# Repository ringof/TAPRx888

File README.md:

CI docs for design

Source: design @ c99de62df487ad7ab04a745b40d1d9217074d0e4
Run: https://github.com/ringof/TAPRx888/actions/runs/30328942444

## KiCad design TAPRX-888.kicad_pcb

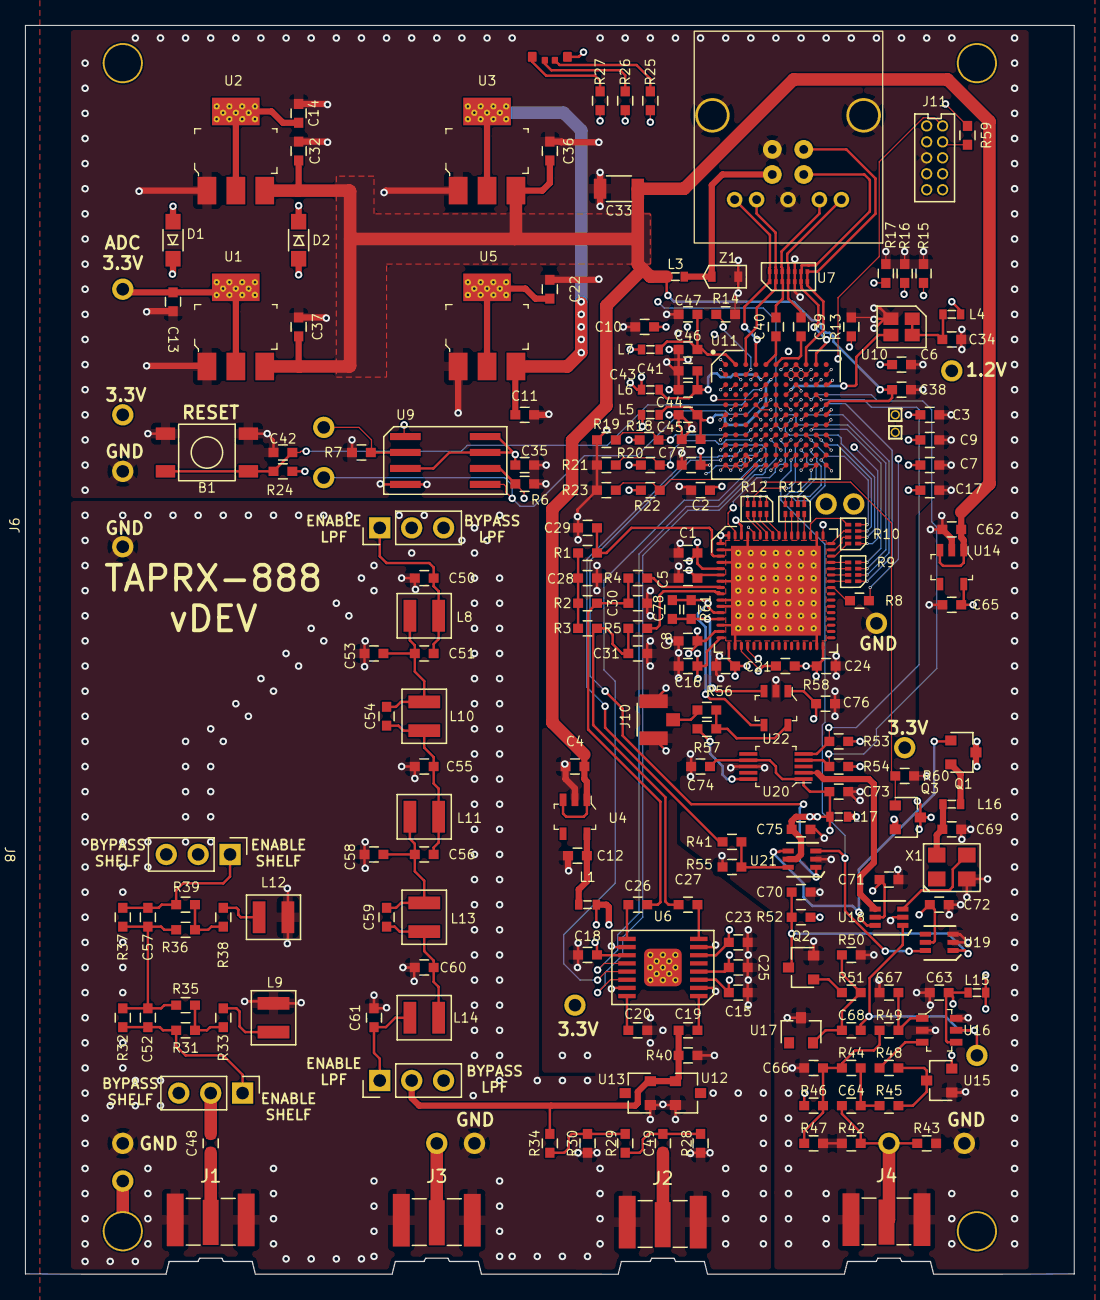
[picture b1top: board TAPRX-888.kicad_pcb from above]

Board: 6 copper layers, 83.5 x 99.4 mm, 223 parts (1 on the bottom side), 156 nets.

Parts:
B1: BUTTON-4p5X4p5
C1, C2, C3, C5, C6, C7, C8, C9, C10, C15, C16, C17, C18, C19, C20, C21, C23, C24, C26, C27, C28, C32, C34, C35, C36, C37, C38, C39, C40, C42, C43, C44, C46, C48, C49, C63, C64, C66, C67, C68, C69, C70, C71, C72, C73, C74, C75, C76, C77: C-0.1-0603; C_0603
C4, C25, C62: C-1u-0603; C_0603
C11, C12, C13, C14, C29, C65: C-10u-0603; C_0603
C22, C41, C45, C47: C-22u-0603; C_0603
C30, C31: C-4.7p-0603; C_0603
C33: C-10u-50V-1206; PAD_1206
C50, C61: C-56p-0603; C_0603
C51: C-12p-0603; C_0603
C52, C57: C-330p-0603; C_0603
C53: C-82p-0603; C_0603
C54: C-39p-0603; C_0603
C55, C58: C-68p-0603; C_0603
C56: C-47p-0603; C_0603
C59: C-22p-0603; C_0603
C60: C-100p-0603; C_0603
C78: C-8.2p-0603; C_0603
D1, D2: Schottky_Pwr_B5819W; SOD-123
D3: LED_RGB_SIDE
H1, H2, H3, H4: MountingHole_M2.5-PTH
J1, J2, J3, J4: CONN_SMA_JACK_EDGE_JLC_With_Nut; SMA_Jack_EdgeMount_JLC_With_Nut
J5: USB-3.0
J6, J7, J8, J9: Conn_01x03; Pin_Header_Straight_1x03_Pitch2.54mm
J10: U.FL-R; HRS_U.FL-R-SMT(01)
J11: Conn_JTAG10-mini; CONN-JTAG10-mini
L1, L4, L5, L6, L7, L15, L16, L17: FBEAD0603-1u-190mA; 0603
L2: TIS_LOGO; TIS-Logo
L3: FBEAD0603_2A; 0603
L8: Inductor-180n-1008; Murata2U
L9, L12: Inductor-820n-1008; Murata2U
L10, L11: Inductor-120n-1008; Murata2U
L13, L14: Inductor-150n-1008; Murata2U
Q1, Q3: PMOS Si2343DS; SOT-23
Q2: MMBT3904; SOT-23
R1, R4, R5: R-4.7-0603; PAD_0603
R2, R3: R-47Ω-0603; PAD_0603
R6, R24: R-100K-0603; PAD_0603
R7: R-2.0K-0603; PAD_0603
R8, R56, R57: R-22Ω-0603; PAD_0603
R9, R10, R11, R12: R-22 0402x4; 4D02
R13: R-6.04K-0603; PAD_0603
R14: R-200-0603; PAD_0603
R15, R16, R17, R25, R26, R27: R-1K-0603; PAD_0603
R18, R19, R20, R21, R22, R23: R-0Ω-0603; PAD_0603
R28, R30, R31, R35, R36, R39: R-51Ω-0603; PAD_0603
R29, R34, R53, R54: R-2.2K-0603; PAD_0603
R32, R37: R-220Ω-0603; PAD_0603
R33, R38: R-10Ω-0603; PAD_0603
R40, R41, R42, R43, R61: R-100-0603; PAD_0603
R44, R49, R50: R-1M-0603; PAD_0603
R45, R48: R-330Ω-0603; PAD_0603
R46, R47, R51, R52, R55, R60: R-10K-0603; PAD_0603
R58, R59: R-47K-0603; PAD_0603
TP1, TP2, TP3, TP4, TP5, TP6, TP7, TP8, TP9, TP10, TP11, TP12, TP13, TP14, TP15, TP16, TP17, TP18, TP19: TP
TP20, TP21: TP-TINY; TP-Tiny
U1, U2, U3: AP2114H-3.3TRG1; SOT-223_THERMAL
U4, U14: LP5907MFX-3.3; SOT-23-5
U5: UMW AMS1117-1.2; SOT-223_THERMAL
U6: AD8370; TSSOP-16-Thermal
U7: TVS-SP3011; SP3011
U8: LTC2208CUP#PBF; QFN-64_EP_9.5x9.5_Pitch0.5mm
U9: MX25L3233FM2I; SOIC-8-dual
U10: XO-19.2MHZ; SMD-2520
U11: CYUSB3014-BZXCT; BGA-121
U12, U13, U15, U17: SOT-23
U16: TLV3501; SOT-23-6
U18, U21: NC7SV157; SC-70-6
U19: 74LVC2G14; SC-70-6_rot90
U20: Si5351A; MSOP-10_W3mm
U22: SN65LVDS1; SOT-23-5
X1: TCXO-27M; TCXO-3225
Z1: PESD5V0U1UA; SOD-323

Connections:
3V3REF: C65.1, L15.2, Q1.3 (D), Q3.3 (D), R53.2, R54.2, TP17.1, U14.5 (OUT)
+1V2: C3.2, C7.2, C10.2, C22.1, C77.2, L6.1, L7.1, TP6.1, U5.2 (OUT), U5.4 (OUT), U11.A7 (AVDD), U11.B10 (VDD@1), U11.C3 (VDD@2), U11.E9 (VDD@3), U11.F11 (VDD@4), U11.H1 (VDD@5), U11.J11 (VDD@7), U11.L5 (VDD@8), U11.L7 (VDD@6)
+3V3: C2.2, C6.2, C9.2, C14.1, C17.2, C35.2, C72.1, D1.2 (A), D2.1 (K), D3.1 (C), J11.1, L4.2, L5.1, R18.2, R20.2, R22.2, R24.1, R52.1, R59.1, TP5.1, U2.2 (OUT), U2.4 (OUT), U9.3 (WPN), U9.7 (HOLDN), U9.8 (VDD), U11.B1 (VIO4), U11.C11 (VIO5), U11.E3 (VIO3), U11.E6 (FSLC[2]), U11.E10 (VBAT), U11.F1 (VIO2), U11.H11 (VIO1@1), U11.L9 (VIO1@2), U19.5 (VCC)
+3V3ADC: C1.2, C5.2, C8.2, C13.1, C16.2, C21.2, C24.2, D1.1 (K), D2.2 (A), R58.1, TP4.1, U1.2 (OUT), U1.4 (OUT), U8.1 (SENSE), U8.5 (VDD_5), U8.6 (VDD), U8.15 (VDD_2), U8.16 (VDD_3), U8.17 (VDD_4), U8.32 (OVDD), U8.49 (OVDD_2), U8.62 (MODE), U8.64 (PGA)
/3.3V-PRE: C11.1, U3.2 (OUT), U3.4 (OUT), U5.3 (IN)
/CLKIN: U10.3 (OUT), U11.D7 (CLKIN)
/Clock/AUTOCLK_N: R41.1, U11.J3 (GPIO37)
/Clock/CLK0: R57.2, U20.10 (CLK0)
/Clock/CLKGEN3.3V: C71.1, C73.2, C74.2, C75.1, C76.1, L17.1, U18.5 (VCC), U20.1 (VDD), U20.7 (VDDO), U21.5 (VCC), U22.1 (VCC)
/Clock/EXTCLKSEL_N: U11.K1 (GPIO35), U21.1 (IN1)
/Clock/EXT_REF_IN: C64.2, J4.1 (In), R42.1, R43.1, TP15.1
/Clock/REFCLK3.3V: C63.2, L15.1, R46.1, U15.2, U16.4 (V+)
/Clock/Vdd5351: L17.2, Q3.2 (S)
/D0: R9.1, U11.F10 (GPIO0)
/D1: R9.2, U11.F9 (GPIO1)
/D2: R9.3, U11.F7 (GPIO2)
/D3: R9.4, U11.G10 (GPIO3)
/D4: R10.1, U11.G9 (GPIO4)
/D5: R10.2, U11.F8 (GPIO5)
/D6: R10.3, U11.H10 (GPIO6)
/D7: R10.4, U11.H9 (GPIO7)
/D8: R11.1, U11.J10 (GPIO8)
/D9: R11.2, U11.J9 (GPIO9)
/D10: R11.3, U11.K11 (GPIO10)
/D11: R11.4, U11.L10 (GPIO11)
/D12: R12.1, U11.K10 (GPIO12)
/D13: R12.2, U11.K9 (GPIO13)
/D14: R12.3, U11.J8 (GPIO14)
/D15: R12.4, U11.G8 (GPIO15)
/DIS_5351: Q3.1 (G), R60.1, U11.J4 (GPIO34)
/DITH: U8.20 (DITH), U11.H5 (GPIO29)
/EXT_REF_ACTIVE: U11.K8 (GPIO17), U19.6, U21.3 (IN0)
/Front_End_Filter/FILTER_OUT: C19.1, J9.2, R34.2, R40.1, U12.1, U13.2
/Front_End_Filter/RF_ATTEN__IN: C49.1, J2.1 (In)
/Front_End_Filter/RF_IN: C48.1, J1.1 (In)
/ID0: R15.1, U11.K2 (GPIO33)
/ID1: R16.1, U11.J2 (GPIO36)
/ID2: R17.1, U11.F2 (GPIO45)
/ID5: R26.1, U11.F4 (GPIO41)
/ID6: R25.1, U11.G6 (GPIO22)
/ID7: R27.1, U11.G7 (GPIO21)
/OVFL: U8.60 (OF+/OFA), U11.G5 (GPIO25)
/PCLK: R8.2, U11.J6 (GPIO16)
/PMODE0: R18.1, R19.1, U11.G4 (GPIO30)
/PMODE1: R20.1, R21.1, U11.H4 (GPIO31)
/PMODE2: R22.1, R23.1, U11.L4 (GPIO32)
/RAND: U8.63 (RAND), U11.H7 (GPIO20)
/RESET_N: B1.3, B1.4, C42.2, J11.10, R24.2, U11.C5 (RESET)
/SAMPLE_CLK_N: C78.2, R61.2, U8.13 (ENC-), U22.3
/SAMPLE_CLK_P: C78.1, R61.1, U8.12 (ENC+), U22.4
/SCL: R54.1, U11.D9 (I2C_GPIO[58]), U20.4 (SCL)
/SDA: R53.1, U11.D10 (I2C_GPIO[59]), U20.5 (SDA)
/SHDN: R58.2, U8.19 (SHDN), U11.J5 (GPIO28)
/SPI_MISO: R7.1, TP9.1, U9.2 (SO), U11.C2 (GPIO55)
/SPI_MOSI: TP10.1, U9.5 (SI), U11.D5 (GPIO56)
/SPI_SCK: R6.1, U9.6 (SCLK), U11.D4 (GPIO53)
/SPI_SSN: U9.1 (CSN), U11.C1 (GPIO54)
/SSRX+: J5.9 (SSRX+), U7.1, U7.14, U11.A4 (SSRXP)
/SSRX-: J5.8 (SSRX-), U7.2, U7.13, U11.A3 (SSRXM)
/SSTX+: C40.1, J5.6 (SSTX+), U7.3, U7.12
/SSTX-: C39.1, J5.5 (SSTX-), U7.4, U7.11
/TCK: J11.4, U11.F6 (TCK)
/TDI: J11.8, U11.E7 (TDI)
/TDO: J11.6, U11.C10 (TDO)
/TMS: J11.2, U11.E8 (TMS)
/TRST: J11.9, R59.2, U11.B11 (TRST)
/USB+: J5.3 (D+), U7.7, U7.8, U11.A9 (DP)
/USB-: J5.2 (D-), U7.6, U7.9, U11.A10 (DM)
/VBUS: C4.1, C32.2, C33.1, C36.2, C37.2, C38.2, C62.1, L3.2, U1.3 (IN), U2.3 (IN), U3.3 (IN), U4.1 (IN), U4.3 (ENA), U11.E11 (VBUS), U14.1 (IN), U14.3 (ENA)
/VCM: C29.1, R1.1, U8.3 (VCM)
/VGA3.3V: C15.2, C18.2, C23.2, C25.1, L1.2, TP3.1, U6.3 (VCCI), U6.4 (PWUP), U6.6 (VCCO), U6.11 (VCCO)
/VGA_CLK: U6.13 (CLK), U11.K5 (GPIO27)
/VGA_D: U6.14 (D), U11.H6 (GPIO26)
/VGA_LE: U6.12 (LE), U11.J1 (GPIO38)
GND: B1.1, B1.2, C1.1, C2.1, C3.1, C4.2, C5.1, C6.1, C7.1, C8.1, C9.1, C10.1, C11.2, C12.2, C13.2, C14.2, C15.1, C16.1, C17.1, C18.1, C20.2, C21.1, C22.2, C23.1, C24.1, C25.2, C28.1, C29.2, C30.2, C31.2, C32.1, C33.2, C34.1, C35.1, C36.1, C37.1, C38.1, C41.2, C42.1, C43.1, C44.1, C45.2, C46.1, C47.2, C50.2, C53.2, C55.2, C58.2, C60.2, C61.2, C62.2, C63.1, C65.2, C66.2, C67.2, C69.1, C70.2, C71.2, C72.2, C73.1, C74.1, C75.2, C76.2, C77.1, J1.2 (Ext), J2.2 (Ext), J3.2 (Ext), J4.2 (Ext), J5.0 (SHELL), J5.4 (GND), J5.7 (SIG_GND), J10.2 (Ext), J11.3, L9.1, L12.1, Q2.2 (E), R6.2, R7.2, R13.2, R14.2, R15.2, R16.2, R17.2, R19.2, R21.2, R23.2, R28.2, R30.2, R40.2, R42.2, R43.2, R47.2, R50.2, R55.2, R60.2, TP2.1, TP7.1, TP8.1, TP14.1, TP16.1, TP19.1, U1.1 (GND), U2.1 (GND), U3.1 (GND), U4.2 (GND), U5.1 (GND), U6.2 (ICOM), U6.7 (OCOM), U6.10 (OCOM), U6.15 (ICOM), U7.5, U7.10, U8.2 (GND_6), U8.4 (GND_2), U8.7 (GND_4), U8.10 (GND_5), U8.11 (GND_7), U8.14 (GND_3), U8.18 (GND), U8.31 (OGND_2), U8.50 (OGND), U8.61 (LVDS), U8.65 (EP), U9.4 (VSS), U10.2 (GND), U11.A1 (U3VSSQ), U11.A8 (VSS@14), U11.B2 (FSLC[0]), U11.B4 (FSLC[1]), U11.B7 (AVSS), U11.B8 (VSS@8), U11.B9 (VSS@9), U11.D8 (VSS@1), U11.E2 (VSS@2), U11.G1 (VSS@3), U11.G11 (VSS@4), U11.K3 (VSS@12), U11.K4 (VSS@10), U11.L1 (VSS@5), U11.L2 (VSS@13), U11.L3 (VSS@11), U11.L6 (VSS@6), U11.L11 (VSS@7), U12.2, U13.1, U14.2 (GND), U15.1, U16.2 (V-), U16.6 (SHDN), U17.3, U18.2 (GND), U19.2 (GND), U19.3, U20.8 (GND), U21.2 (GND), U22.2 (GND), X1.2 (GND), Z1.2
unnamed: C26.2, C30.1, R2.1, R4.1
unnamed: C27.2, C31.1, R3.2, R5.1
unnamed: C28.2, R1.2, R2.2, R3.1
unnamed: C49.2, R28.1, R29.1
unnamed: C51.2, C53.1, C54.1, L8.2, L10.1
unnamed: C52.2, C57.1, R32.2, R35.2, R36.1, R37.1
unnamed: C54.2, C55.1, C56.1, L10.2, L11.1
unnamed: C56.2, C58.1, C59.1, L11.2, L13.1
unnamed: C59.2, C60.1, L13.2, L14.1
unnamed: C64.1, R44.2, R45.2
unnamed: C66.1, R44.1, R46.2, R47.1, R49.1
unnamed: C68.1, R50.1, R51.2, U17.2
unnamed: D3.2 (B), R25.2
unnamed: D3.3 (G), R26.2
unnamed: D3.4 (R), R27.2
unnamed: H1.1, TP13.1
unnamed: J3.1 (In), TP1.1
unnamed: J5.1 (V+), L3.1, Z1.1
unnamed: C50.1, C51.1, J6.1, L8.1
unnamed: J6.2, J8.2
unnamed: J6.3, J9.3
unnamed: C52.1, J7.1, R31.1, R32.1
unnamed: C48.2, J7.2
unnamed: J7.3, J8.3
unnamed: C57.2, J8.1, R37.2, R39.2
unnamed: C61.1, J9.1, L14.2
unnamed: J10.1 (In), R56.1
unnamed: L9.2, R33.2
unnamed: L12.2, R38.2
unnamed: Q1.1 (G), U18.6 (SEL), U21.4 (Z)
unnamed: L16.2, Q1.2 (S)
unnamed: Q2.1 (B), R51.1
unnamed: C70.1, Q2.3 (C), R52.2, U19.1
unnamed: R29.2, R30.1, R34.1
unnamed: R31.2, R33.1, R35.1
unnamed: R36.2, R38.1, R39.1
unnamed: R45.1, R48.2, U15.3
unnamed: R56.2, R57.1, U22.5
unnamed: C12.1, L1.1, U4.5 (OUT)
unnamed: C19.2, U6.1 (IN+)
unnamed: C20.1, U6.16 (IN-)
unnamed: C27.1, U6.8 (OUT+)
unnamed: C26.1, U6.9 (OUT-)
unnamed: R4.2, U8.8 (AIN+)
unnamed: R5.2, U8.9 (AIN-)
unnamed: R9.8, U8.42 (D8+/DA0)
unnamed: R8.1, U8.41 (D8-/CLKOUTA)
unnamed: R9.6, U8.44 (D9+/DA2)
unnamed: R9.7, U8.43 (D9-/DA1)
unnamed: R10.8, U8.46 (D10+/DA4)
unnamed: R9.5, U8.45 (D10-/DA3)
unnamed: R10.6, U8.48 (D11+/DA6)
unnamed: R10.7, U8.47 (D11-/DA5)
unnamed: R11.8, U8.52 (D12+/DA8)
unnamed: R10.5, U8.51 (D12-_/DA7)
unnamed: R11.6, U8.54 (D13+/DA10)
unnamed: R11.7, U8.53 (D13-/DA9)
unnamed: R12.8, U8.56 (D14+/DA12)
unnamed: R11.5, U8.55 (D14-/DA11)
unnamed: R12.6, U8.58 (D15+/DA14)
unnamed: R12.7, U8.57 (D15-/DA13)
unnamed: R12.5, U8.59 (OF-/DA15)
unnamed: C34.2, L4.1, U10.1 (TS-N), U10.4 (VDD)
unnamed: C44.2, C45.1, L5.2, U11.B6 (CVDDQ)
unnamed: TP11.1, U11.K7 (GPIO18)
unnamed: TP12.1, U11.J7 (GPIO19)
unnamed: TP20.1, U11.E5 (GPIO48)
unnamed: TP21.1, U11.E4 (GPIO49)
unnamed: R13.1, U11.C8 (R_USB2)
unnamed: R14.1, U11.B3 (R_USB3)
unnamed: C39.2, U11.A6 (SSTXM)
unnamed: C40.2, U11.A5 (SSTXP)
unnamed: C46.2, C47.1, L7.2, U11.A2 (U3RXVDDQ)
unnamed: C41.1, C43.2, L6.2, U11.B5 (U3TXVDDQ)
unnamed: R48.1, U16.3 (IN+)
unnamed: C67.1, R49.2, U16.1 (IN-)
unnamed: C68.2, TP18.1, U16.5 (OUT), U18.1 (IN1)
unnamed: U18.3 (IN0), X1.3 (OUT)
unnamed: U18.4 (Z), U20.2 (XA)
unnamed: R41.2, R55.1, U21.6 (SEL)
unnamed: C69.2, L16.1, X1.4 (VDD)

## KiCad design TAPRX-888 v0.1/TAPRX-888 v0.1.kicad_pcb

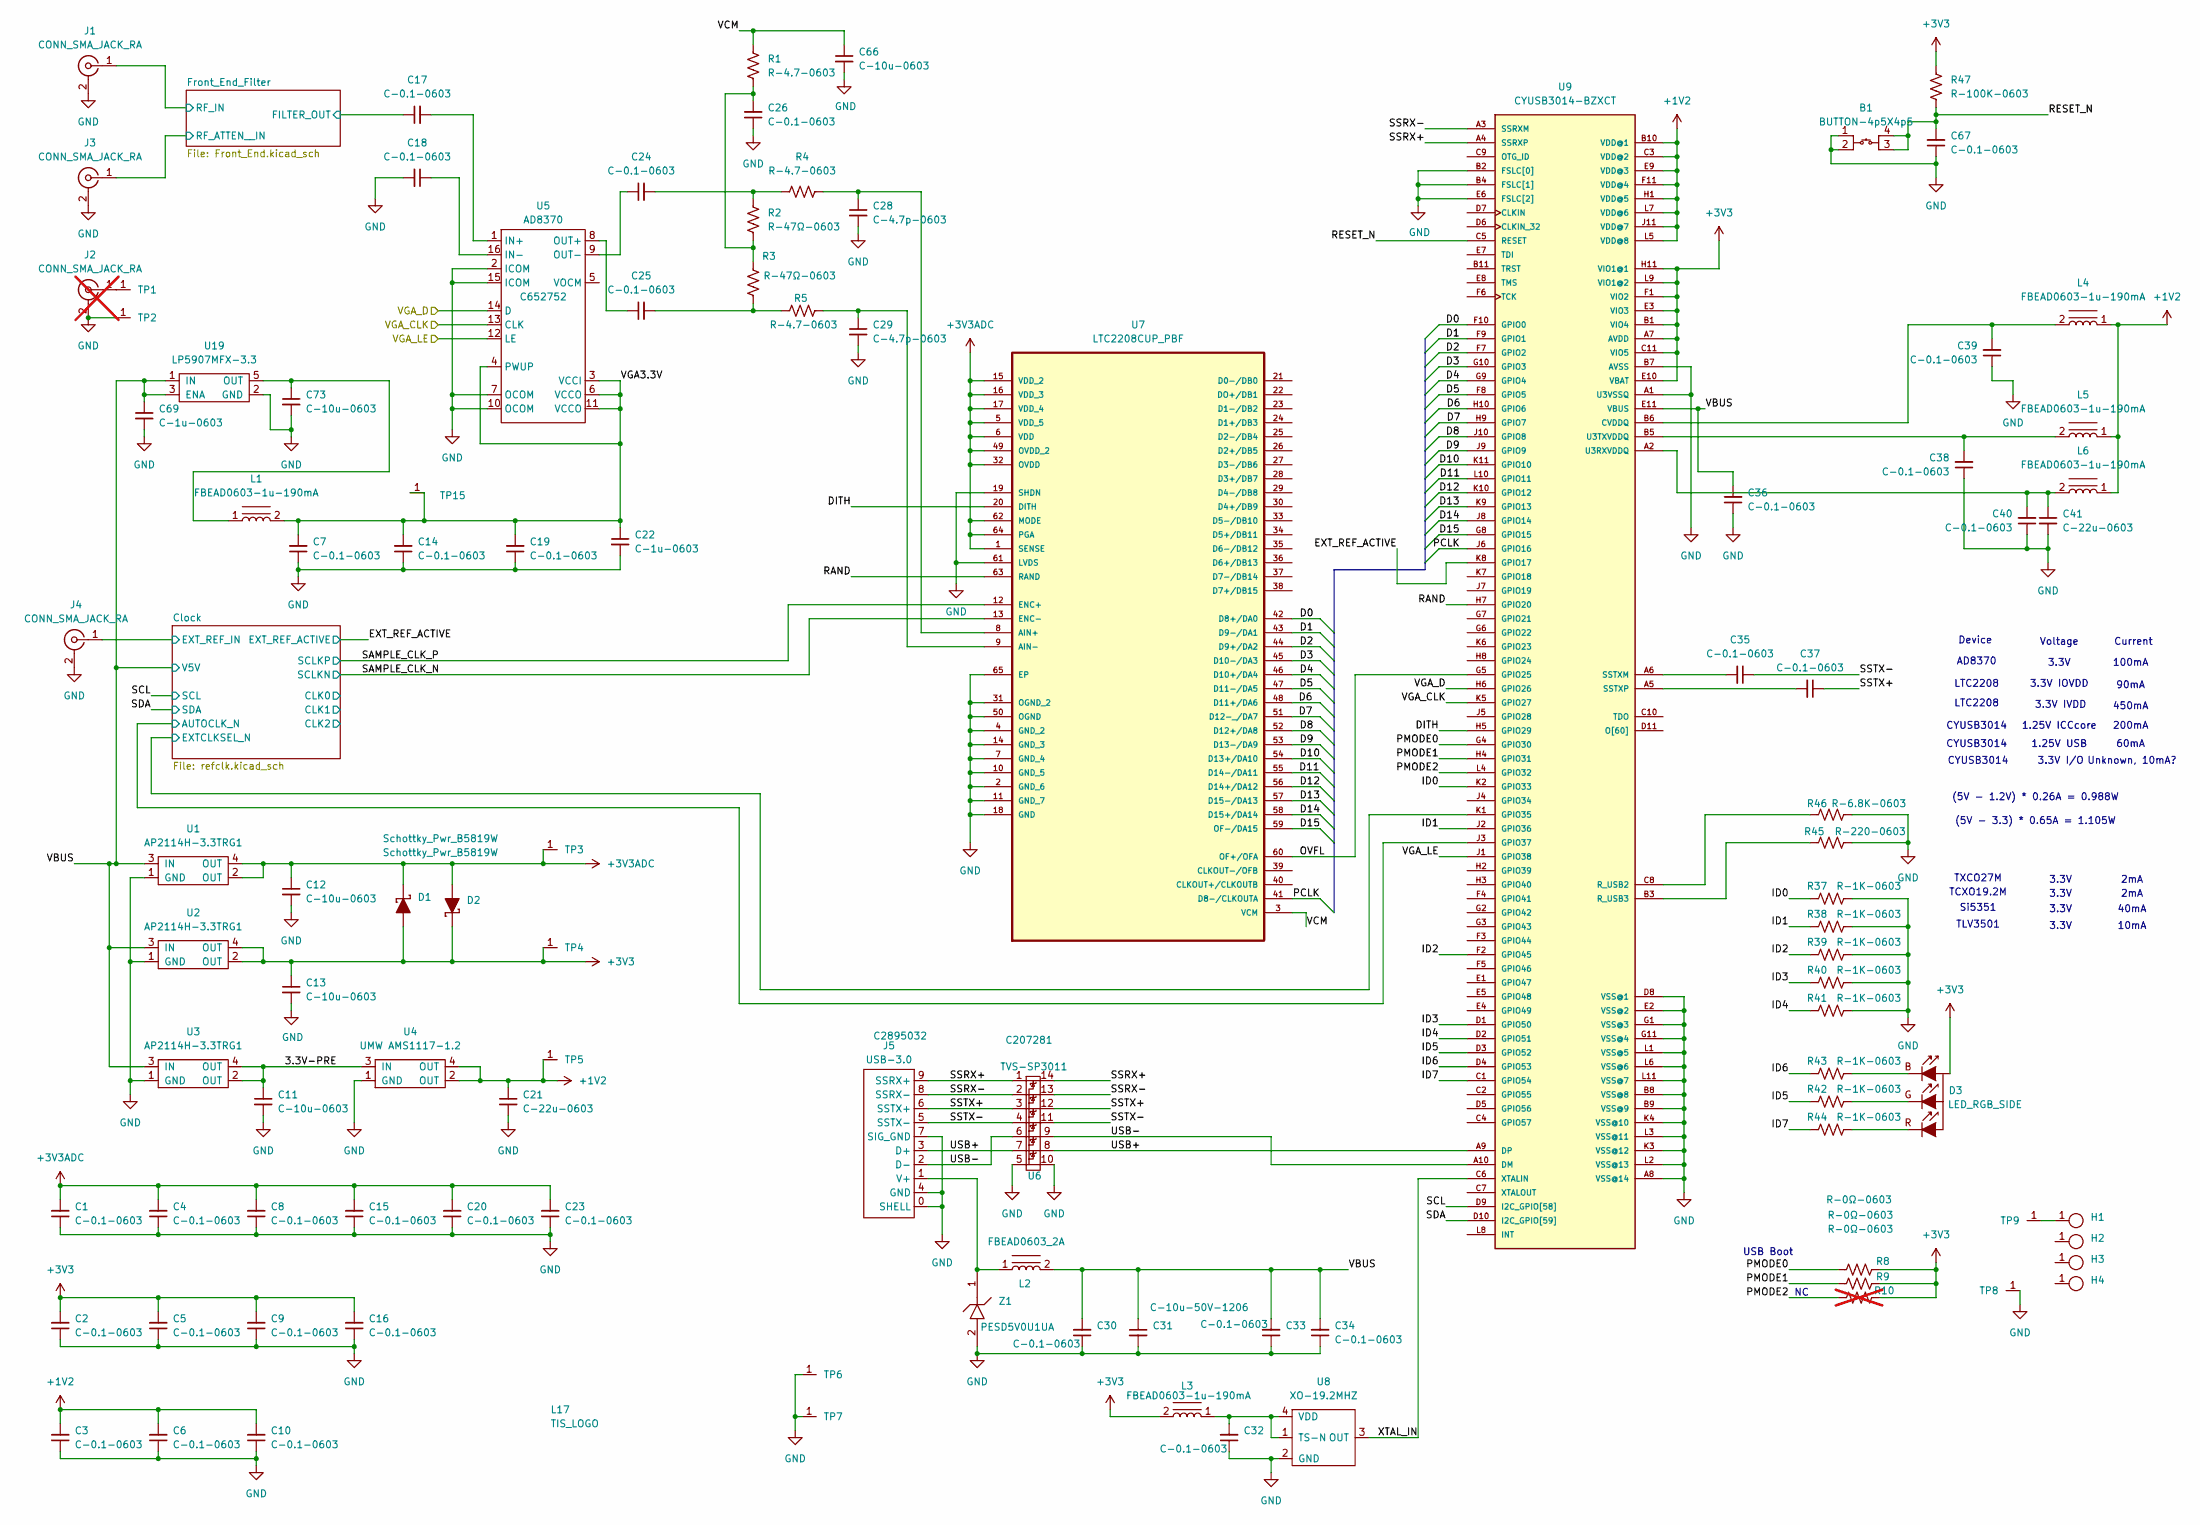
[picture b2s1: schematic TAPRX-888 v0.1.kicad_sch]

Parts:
B1: BUTTON-4p5X4p5; LCSC Part # C410371
C1, C2, C3, C4, C5, C6, C7, C8, C9, C10, C14, C15, C16, C17, C18, C19, C20, C23, C24, C25, C26, C30, C32, C33, C34, C35, C36, C37, C38, C39, C40, C67: C-0.1-0603; C_0603; LCSC Part # C14663
C11, C12, C13, C66, C73: C-10u-0603; PAD_0603; LCSC Part # C96446
C21, C41: C-22u-0603; PAD_0603; LCSC Part # C59461
C22, C69: C-1u-0603; PAD_0603; LCSC Part # C15849
C28, C29: C-4.7p-0603; C_0603; LCSC Part # C1669
C31: C-10u-50V-1206; PAD_1206; LCSC Part # C13585
D1, D2: Schottky_Pwr_B5819W; SOD-123; LCSC Part # C8598
D3: LED_RGB_SIDE; LCSC Part # C389528
H1, H2, H3, H4: MountingHole_M2.5-PTH
J1, J3, J4: CONN_SMA_JACK_RA; SMA-RA-Jack; LCSC Part # C91455
J2: CONN_SMA_JACK_RA; SMA-RA-Jack; LCSC Part # C91455; not fitted
J5: USB-3.0; LCSC Part # C2895032
L1, L3, L4, L5, L6: FBEAD0603-1u-190mA; 0603; LCSC Part # C307748
L2: FBEAD0603_2A; 0603; LCSC Part # C14709
L17: TIS_LOGO; TIS-Logo
R1, R4, R5: R-4.7-0603; PAD_0603; LCSC Part # C23164
R2, R3: R-47Ω-0603; PAD_0603; LCSC Part # C23179
R8, R9: R-0Ω-0603; PAD_0603; LCSC Part # C21189
R10: R-0Ω-0603; PAD_0603; LCSC Part # C21189; not fitted
R37, R38, R39, R40, R41, R42, R43, R44: R-1K-0603; PAD_0603; LCSC Part # C21190
R45: R-220-0603; PAD_0603; LCSC Part # C107696
R46: R-6.8K-0603; PAD_0603; LCSC Part # C114632
R47: R-100K-0603; PAD_0603; LCSC Part # C25803
TP1, TP2, TP3, TP4, TP5, TP6, TP7, TP8, TP9, TP15: TP
U1, U2, U3: AP2114H-3.3TRG1; SOT-223_THERMAL; LCSC Part # C150716
U4: UMW AMS1117-1.2; SOT-223_THERMAL; LCSC Part # C347218
U5: AD8370; TSSOP-16-Thermal; LCSC Part # C652752
U6: TVS-SP3011; SP3011; LCSC Part # C207281
U7: LTC2208CUP_PBF; QFN-64_EP_9.5x9.5_Pitch0.5mm; MPN LTC2208CUP#PBF#PBF; LCSC Part # C679544
U8: XO-19.2MHZ; SMD-2520; LCSC Part # C49304731
U9: CYUSB3014-BZXCT; BGA-121; DigiKey_Part_Number 448-CYUSB3014-BZXCTTR-ND
U19: LP5907MFX-3.3; SOT-23-5; LCSC Part # C80670
Z1: PESD5V0U1UA; SOD-323; LCSC Part # C5380401

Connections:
+1V2: C3.2, C6.2, C10.2, C21.1, L4.1, L5.1, L6.1, TP5.1, U4.2 (OUT), U4.4 (OUT), U9.B10 (VDD@1), U9.C3 (VDD@2), U9.E9 (VDD@3), U9.F11 (VDD@4), U9.H1 (VDD@5), U9.J11 (VDD@7), U9.L5 (VDD@8), U9.L7 (VDD@6)
+3V3: C2.2, C5.2, C9.2, C13.1, C16.2, D1.2 (A), D2.1 (K), D3.1 (C), L3.2, R8.2, R9.2, R10.2, R47.1, TP4.1, U2.2 (OUT), U2.4 (OUT), U9.A7 (AVDD), U9.B1 (VIO4), U9.C11 (VIO5), U9.E3 (VIO3), U9.E10 (VBAT), U9.F1 (VIO2), U9.H11 (VIO1@1), U9.L9 (VIO1@2); also elsewhere on the board
+3V3ADC: C1.2, C4.2, C8.2, C12.1, C15.2, C20.2, C23.2, D1.1 (K), D2.2 (A), TP3.1, U1.2 (OUT), U1.4 (OUT), U7.1 (SENSE), U7.5 (VDD_5), U7.6 (VDD), U7.15 (VDD_2), U7.16 (VDD_3), U7.17 (VDD_4), U7.32 (OVDD), U7.49 (OVDD_2), U7.62 (MODE), U7.64 (PGA)
/3.3V-PRE: C11.1, U3.2 (OUT), U3.4 (OUT), U4.3 (IN)
/Clock/AUTOCLK_N: U9.J3 (GPIO37); also elsewhere on the board
/Clock/EXTCLKSEL_N: U9.K1 (GPIO35); also elsewhere on the board
/Clock/EXT_REF_IN: J4.1 (In); also elsewhere on the board
/D0: U7.42 (D8+/DA0), U9.F10 (GPIO0)
/D1: U7.43 (D9-/DA1), U9.F9 (GPIO1)
/D2: U7.44 (D9+/DA2), U9.F7 (GPIO2)
/D3: U7.45 (D10-/DA3), U9.G10 (GPIO3)
/D4: U7.46 (D10+/DA4), U9.G9 (GPIO4)
/D5: U7.47 (D11-/DA5), U9.F8 (GPIO5)
/D6: U7.48 (D11+/DA6), U9.H10 (GPIO6)
/D7: U7.51 (D12-_/DA7), U9.H9 (GPIO7)
/D8: U7.52 (D12+/DA8), U9.J10 (GPIO8)
/D9: U7.53 (D13-/DA9), U9.J9 (GPIO9)
/D10: U7.54 (D13+/DA10), U9.K11 (GPIO10)
/D11: U7.55 (D14-/DA11), U9.L10 (GPIO11)
/D12: U7.56 (D14+/DA12), U9.K10 (GPIO12)
/D13: U7.57 (D15-/DA13), U9.K9 (GPIO13)
/D14: U7.58 (D15+/DA14), U9.J8 (GPIO14)
/D15: U7.59 (OF-/DA15), U9.G8 (GPIO15)
/DITH: U7.20 (DITH), U9.H5 (GPIO29)
/EXT_REF_ACTIVE: U9.K8 (GPIO17); also elsewhere on the board
/Front_End_Filter/FILTER_OUT: C17.1; also elsewhere on the board
/Front_End_Filter/RF_ATTEN__IN: J3.1 (In); also elsewhere on the board
/Front_End_Filter/RF_IN: J1.1 (In); also elsewhere on the board
/ID0: R37.1, U9.K2 (GPIO33)
/ID1: R38.1, U9.J2 (GPIO36)
/ID2: R39.1, U9.F2 (GPIO45)
/ID3: R40.1, U9.D1 (GPIO50)
/ID4: R41.1, U9.D2 (GPIO51)
/ID5: R42.1, U9.D3 (GPIO52)
/ID6: R43.1, U9.D4 (GPIO53)
/ID7: R44.1, U9.C1 (GPIO54)
/OVFL: U7.60 (OF+/OFA), U9.G5 (GPIO25)
/PCLK: U7.41 (D8-/CLKOUTA), U9.J6 (GPIO16)
/PMODE0: R8.1, U9.G4 (GPIO30)
/PMODE1: R9.1, U9.H4 (GPIO31)
/PMODE2: R10.1, U9.L4 (GPIO32)
/RAND: U7.63 (RAND), U9.H7 (GPIO20)
/RESET_N: B1.3, B1.4, C67.2, R47.2, U9.C5 (RESET)
/SAMPLE_CLK_N: U7.13 (ENC-); also elsewhere on the board
/SAMPLE_CLK_P: U7.12 (ENC+); also elsewhere on the board
/SCL: U9.D9 (I2C_GPIO[58]); also elsewhere on the board
/SDA: U9.D10 (I2C_GPIO[59]); also elsewhere on the board
/SSRX+: J5.9 (SSRX+), U6.1, U6.14, U9.A4 (SSRXP)
/SSRX-: J5.8 (SSRX-), U6.2, U6.13, U9.A3 (SSRXM)
/SSTX+: C37.1, J5.6 (SSTX+), U6.3, U6.12
/SSTX-: C35.1, J5.5 (SSTX-), U6.4, U6.11
/USB+: J5.3 (D+), U6.7, U6.8, U9.A9 (DP)
/USB-: J5.2 (D-), U6.6, U6.9, U9.A10 (DM)
/VBUS: C30.2, C31.1, C33.2, C34.2, C36.2, C69.1, L2.2, U1.3 (IN), U2.3 (IN), U3.3 (IN), U9.E11 (VBUS), U19.1 (IN), U19.3 (ENA); also elsewhere on the board
/VCM: C66.1, R1.1, U7.3 (VCM)
/VGA3.3V: C7.2, C14.2, C19.2, C22.1, L1.2, TP15.1, U5.3 (VCCI), U5.4 (PWUP), U5.6 (VCCO), U5.11 (VCCO)
/VGA_CLK: U5.13 (CLK), U9.K5 (GPIO27)
/VGA_D: U5.14 (D), U9.H6 (GPIO26)
/VGA_LE: U5.12 (LE), U9.J1 (GPIO38)
/XTAL_IN: U8.3 (OUT), U9.C6 (XTALIN)
GND: B1.1, B1.2, C1.1, C2.1, C3.1, C4.1, C5.1, C6.1, C7.1, C8.1, C9.1, C10.1, C11.2, C12.2, C13.2, C14.1, C15.1, C16.1, C18.2, C19.1, C20.1, C21.2, C22.2, C23.1, C26.1, C28.2, C29.2, C30.1, C31.2, C32.1, C33.1, C34.1, C36.1, C38.1, C39.1, C40.1, C41.2, C66.2, C67.1, C69.2, C73.2, J1.2 (Ext), J2.2 (Ext), J3.2 (Ext), J4.2 (Ext), J5.0 (SHELL), J5.4 (GND), J5.7 (SIG_GND), R37.2, R38.2, R39.2, R40.2, R41.2, R45.2, R46.2, TP2.1, TP6.1, TP7.1, TP8.1, U1.1 (GND), U2.1 (GND), U3.1 (GND), U4.1 (GND), U5.2 (ICOM), U5.7 (OCOM), U5.10 (OCOM), U5.15 (ICOM), U6.5, U6.10, U7.2 (GND_6), U7.4 (GND_2), U7.7 (GND_4), U7.10 (GND_5), U7.11 (GND_7), U7.14 (GND_3), U7.18 (GND), U7.19 (SHDN), U7.31 (OGND_2), U7.50 (OGND), U7.61 (LVDS), U7.65 (EP), U8.2 (GND), U9.A1 (U3VSSQ), U9.A8 (VSS@14), U9.B2 (FSLC[0]), U9.B4 (FSLC[1]), U9.B7 (AVSS), U9.B8 (VSS@8), U9.B9 (VSS@9), U9.D8 (VSS@1), U9.E2 (VSS@2), U9.E6 (FSLC[2]), U9.G1 (VSS@3), U9.G11 (VSS@4), U9.K3 (VSS@12), U9.K4 (VSS@10), U9.L1 (VSS@5), U9.L2 (VSS@13), U9.L3 (VSS@11), U9.L6 (VSS@6), U9.L11 (VSS@7), U19.2 (GND), Z1.2; also elsewhere on the board
unnamed: C24.2, R2.1, R4.1
unnamed: C25.2, R3.2, R5.1
unnamed: C26.2, R1.2, R2.2, R3.1
unnamed: D3.2 (B), R43.2
unnamed: D3.3 (G), R42.2
unnamed: D3.4 (R), R44.2
unnamed: H1.1, TP9.1
unnamed: J2.1 (In), TP1.1
unnamed: J5.1 (V+), L2.1, Z1.1
unnamed: C17.2, U5.1 (IN+)
unnamed: C18.1, U5.16 (IN-)
unnamed: C25.1, U5.8 (OUT+)
unnamed: C24.1, U5.9 (OUT-)
unnamed: C28.1, R4.2, U7.8 (AIN+)
unnamed: C29.1, R5.2, U7.9 (AIN-)
unnamed: C32.2, L3.1, U8.1 (TS-N), U8.4 (VDD)
unnamed: C39.2, L4.2, U9.B6 (CVDDQ)
unnamed: R46.1, U9.C8 (R_USB2)
unnamed: R45.1, U9.B3 (R_USB3)
unnamed: C35.2, U9.A6 (SSTXM)
unnamed: C37.2, U9.A5 (SSTXP)
unnamed: C40.2, C41.1, L6.2, U9.A2 (U3RXVDDQ)
unnamed: C38.2, L5.2, U9.B5 (U3TXVDDQ)
unnamed: C73.1, L1.1, U19.5 (OUT)

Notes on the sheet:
3.3V
CYUSB3014
TCXO19.2M
3.3V IOVDD
2mA
TXCO27M
1.25V USB
LTC2208
450mA
3.3V IVDD
200mA
10mA
100mA
Voltage
TLV3501
(5V - 3.3) * 0.65A = 1.105W
Si5351
USB Boot
90mA
1.25V ICCcore
Unknown, 10mA?
AD8370
40mA
60mA
Device
Current
3.3V I/O
(5V - 1.2V) * 0.26A = 0.988W

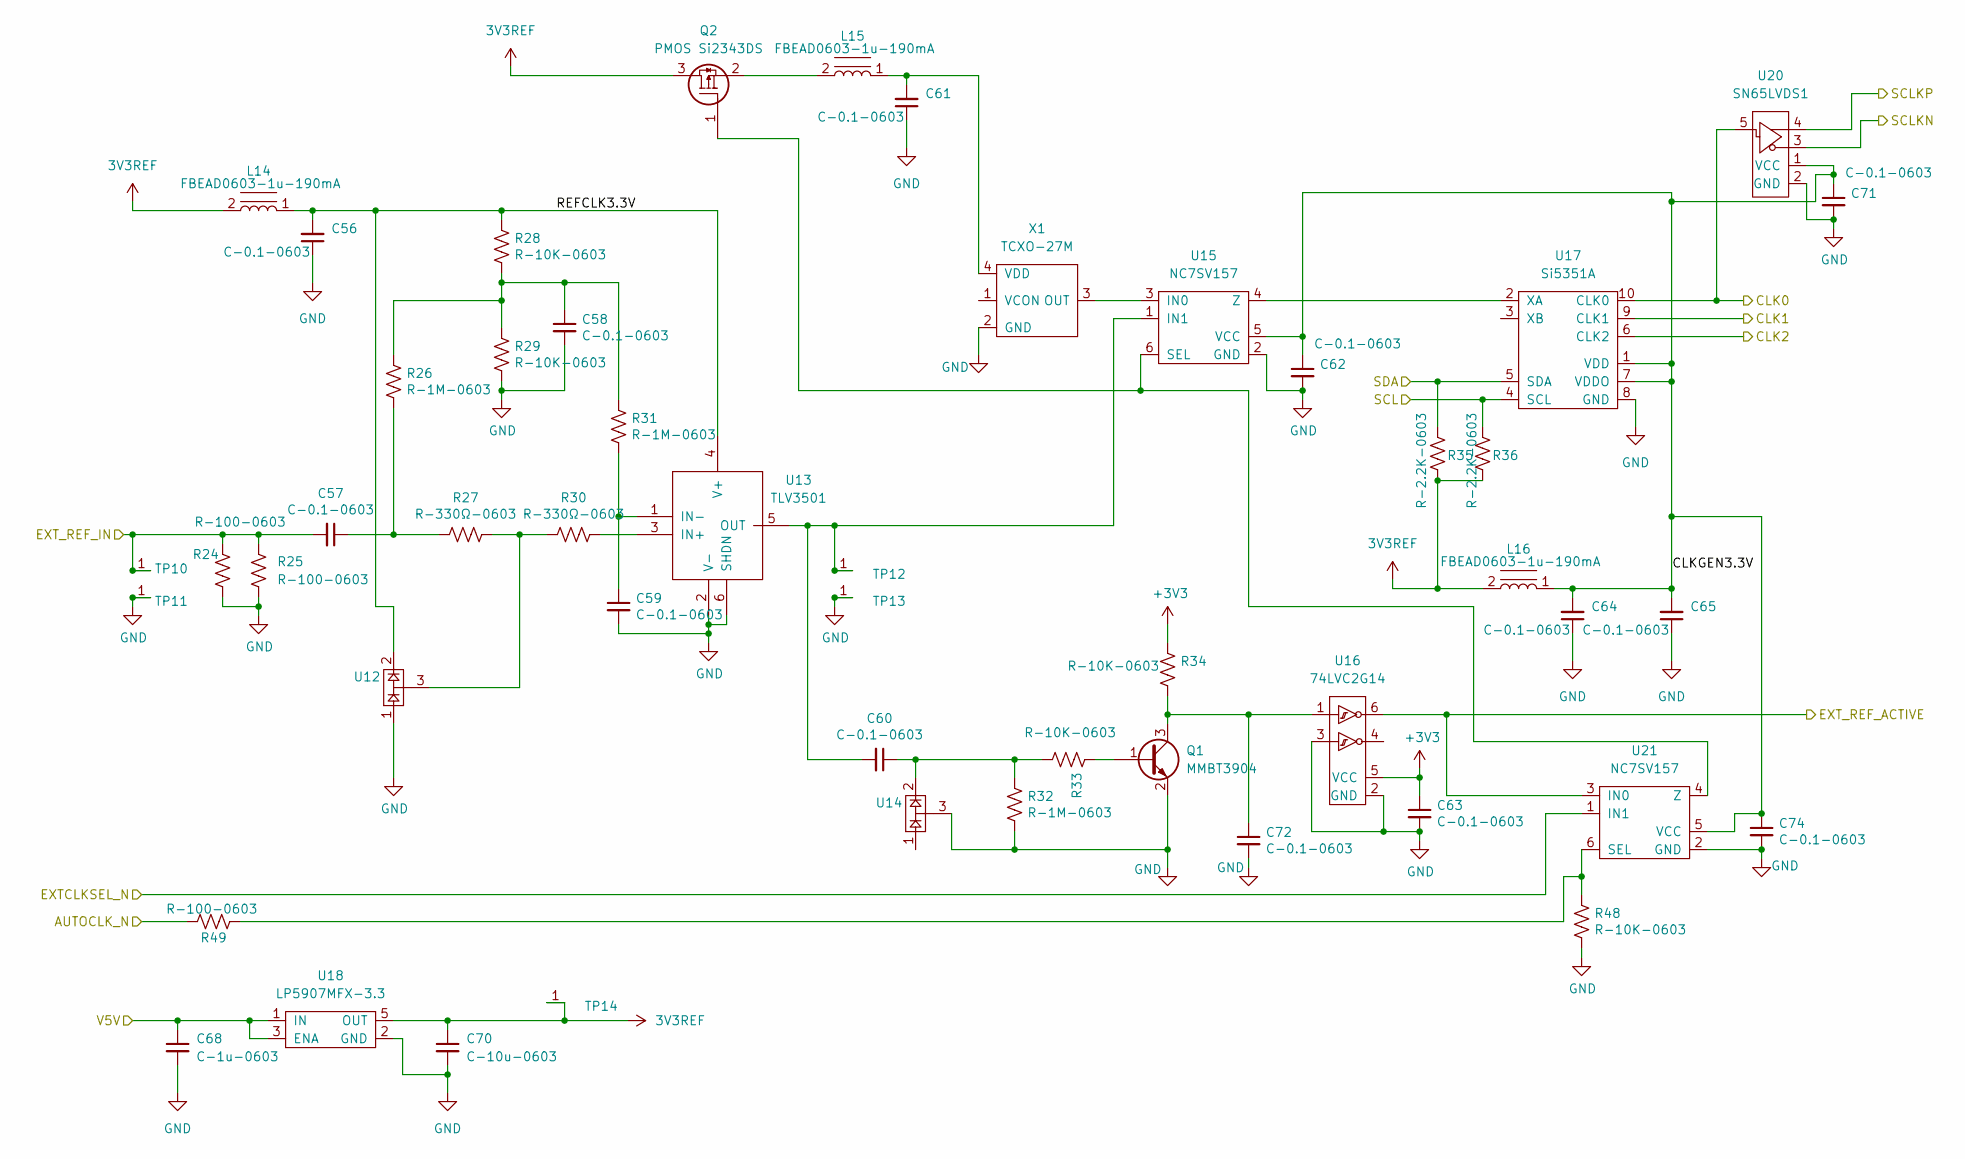
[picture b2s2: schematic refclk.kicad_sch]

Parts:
C56, C57, C58, C59, C60, C61, C62, C63, C64, C65, C71, C72, C74: C-0.1-0603; C_0603; LCSC Part # C14663
C68: C-1u-0603; PAD_0603; LCSC Part # C15849
C70: C-10u-0603; PAD_0603; LCSC Part # C96446
L14, L15, L16: FBEAD0603-1u-190mA; 0603; LCSC Part # C307748
Q1: MMBT3904; SOT-23; LCSC Part # C20526
Q2: PMOS Si2343DS; SOT-23; LCSC Part # C6903
R24, R25, R49: R-100-0603; PAD_0603; LCSC Part # C22775
R26, R31, R32: R-1M-0603; PAD_0603; LCSC Part # C22935
R27, R30: R-330Ω-0603; PAD_0603; LCSC Part # C23138
R28, R29, R33, R34, R48: R-10K-0603; PAD_0603; LCSC Part # C25804
R35, R36: R-2.2K-0603; PAD_0603; LCSC Part # C4190
TP10, TP11, TP12, TP13, TP14: TP
U12, U14: SOT-23; LCSC Part # C78088
U13: TLV3501; SOT-23-6; LCSC Part # C193413
U15, U21: NC7SV157; SC-70-6; LCSC Part # C184123
U16: 74LVC2G14; SC-70-6_rot90; LCSC Part # C19829575
U17: Si5351A; MSOP-10_W3mm; LCSC Part # C504891
U18: LP5907MFX-3.3; SOT-23-5; LCSC Part # C80670
U20: SN65LVDS1; SOT-23-5; LCSC Part # C465731
X1: TCXO-27M; TCXO-3225; LCSC Part # C5203549

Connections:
3V3REF: C70.1, L14.2, L16.2, Q2.3 (D), R35.2, R36.2, TP14.1, U18.5 (OUT)
+3V3: C63.1, R34.1, U16.5 (VCC); also elsewhere on the board
/Clock/AUTOCLK_N: R49.1; also elsewhere on the board
/Clock/CLK0: U17.10 (CLK0), U20.5
/Clock/CLK1: U17.9 (CLK1)
/Clock/CLK2: U17.6 (CLK2)
/Clock/CLKGEN3.3V: C62.1, C64.2, C65.2, C71.1, C74.1, L16.1, U15.5 (VCC), U17.1 (VDD), U17.7 (VDDO), U20.1 (VCC), U21.5 (VCC)
/Clock/EXTCLKSEL_N: U21.1 (IN1); also elsewhere on the board
/Clock/EXT_REF_IN: C57.2, R24.1, R25.1, TP10.1; also elsewhere on the board
/Clock/REFCLK3.3V: C56.2, L14.1, R28.1, U12.2, U13.4 (V+)
/EXT_REF_ACTIVE: U16.6, U21.3 (IN0); also elsewhere on the board
/SAMPLE_CLK_N: U20.3; also elsewhere on the board
/SAMPLE_CLK_P: U20.4; also elsewhere on the board
/SCL: R36.1, U17.4 (SCL); also elsewhere on the board
/SDA: R35.1, U17.5 (SDA); also elsewhere on the board
/VBUS: C68.1, U18.1 (IN), U18.3 (ENA); also elsewhere on the board
GND: C56.1, C58.2, C59.2, C61.1, C62.2, C63.2, C64.1, C65.1, C68.2, C70.2, C71.2, C72.2, C74.2, Q1.2 (E), R24.2, R25.2, R29.2, R32.2, R48.2, TP11.1, TP13.1, U12.1, U13.2 (V-), U13.6 (SHDN), U14.3, U15.2 (GND), U16.2 (GND), U16.3, U17.8 (GND), U18.2 (GND), U20.2 (GND), U21.2 (GND), X1.2 (GND); also elsewhere on the board
unnamed: C57.1, R26.2, R27.2
unnamed: C58.1, R26.1, R28.2, R29.1, R31.1
unnamed: C60.1, R32.1, R33.2, U14.2
unnamed: Q1.1 (B), R33.1
unnamed: C72.1, Q1.3 (C), R34.2, U16.1
unnamed: Q2.1 (G), U15.6 (SEL), U21.4 (Z)
unnamed: L15.2, Q2.2 (S)
unnamed: R27.1, R30.2, U12.3
unnamed: R30.1, U13.3 (IN+)
unnamed: C59.1, R31.2, U13.1 (IN-)
unnamed: C60.2, TP12.1, U13.5 (OUT), U15.1 (IN1)
unnamed: U15.3 (IN0), X1.3 (OUT)
unnamed: U15.4 (Z), U17.2 (XA)
unnamed: R48.1, R49.2, U21.6 (SEL)
unnamed: C61.2, L15.1, X1.4 (VDD)

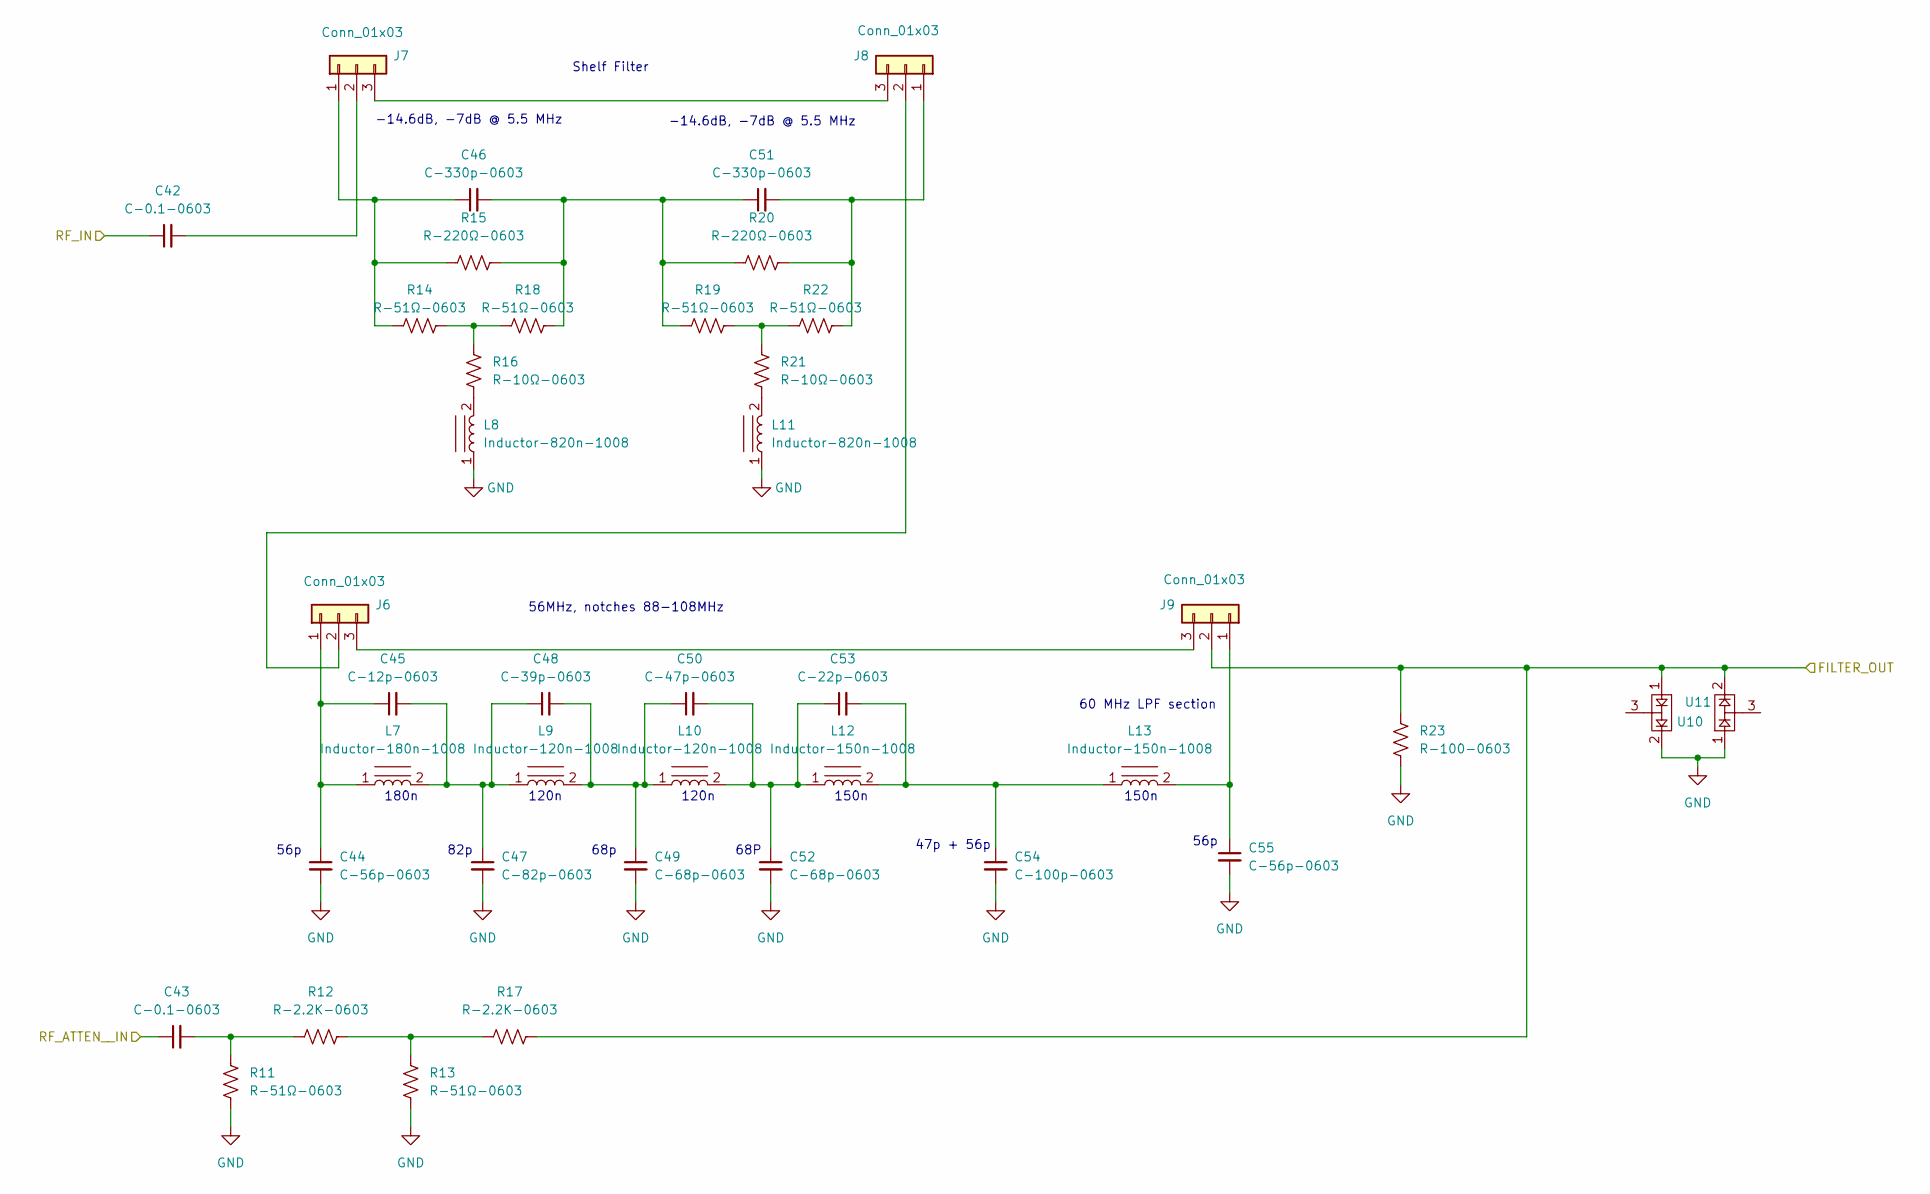
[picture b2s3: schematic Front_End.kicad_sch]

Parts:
C42, C43: C-0.1-0603; C_0603; LCSC Part # C14663
C44, C55: C-56p-0603; C_0603; LCSC Part # C107053
C45: C-12p-0603; PAD_0603; LCSC Part # C576801
C46, C51: C-330p-0603; PAD_0603; LCSC Part # C327088
C47: C-82p-0603; C_0603; LCSC Part # C1683
C48: C-39p-0603; C_0603; LCSC Part # C107049
C49, C52: C-68p-0603; C_0603; LCSC Part # C62782
C50: C-47p-0603; C_0603; LCSC Part # C105622
C53: C-22p-0603; C_0603; LCSC Part # C105620
C54: C-100p-0603; PAD_0603; LCSC Part # C14665
J6, J7, J8, J9: Conn_01x03; Pin_Header_Straight_1x03_Pitch2.54mm; LCSC Part # C2937625
L7: Inductor-180n-1008; Murata2U; LCSC Part # C162664
L8, L11: Inductor-820n-1008; Murata2U; LCSC Part # C701161
L9, L10: Inductor-120n-1008; Murata2U; LCSC Part # C2044072
L12, L13: Inductor-150n-1008; Murata2U; LCSC Part # C2043109
R11, R13, R14, R18, R19, R22: R-51Ω-0603; PAD_0603; LCSC Part # C23197
R12, R17: R-2.2K-0603; PAD_0603; LCSC Part # C4190
R15, R20: R-220Ω-0603; PAD_0603; LCSC Part # C22962
R16, R21: R-10Ω-0603; PAD_0603; LCSC Part # C22859
R23: R-100-0603; PAD_0603; LCSC Part # C22775
U10, U11: SOT-23; LCSC Part # C78088

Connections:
/Front_End_Filter/FILTER_OUT: J9.2, R17.2, R23.1, U10.1, U11.2; also elsewhere on the board
/Front_End_Filter/RF_ATTEN__IN: C43.1; also elsewhere on the board
/Front_End_Filter/RF_IN: C42.1; also elsewhere on the board
GND: C44.2, C47.2, C49.2, C52.2, C54.2, C55.2, L8.1, L11.1, R11.2, R13.2, R23.2, U10.2, U11.1; also elsewhere on the board
unnamed: C43.2, R11.1, R12.1
unnamed: C45.2, C47.1, C48.1, L7.2, L9.1
unnamed: C46.2, C51.1, R15.2, R18.2, R19.1, R20.1
unnamed: C48.2, C49.1, C50.1, L9.2, L10.1
unnamed: C50.2, C52.1, C53.1, L10.2, L12.1
unnamed: C53.2, C54.1, L12.2, L13.1
unnamed: C44.1, C45.1, J6.1, L7.1
unnamed: J6.2, J8.2
unnamed: J6.3, J9.3
unnamed: C46.1, J7.1, R14.1, R15.1
unnamed: C42.2, J7.2
unnamed: J7.3, J8.3
unnamed: C51.2, J8.1, R20.2, R22.2
unnamed: C55.1, J9.1, L13.2
unnamed: L8.2, R16.2
unnamed: L11.2, R21.2
unnamed: R12.2, R13.1, R17.1
unnamed: R14.2, R16.1, R18.1
unnamed: R19.2, R21.1, R22.1

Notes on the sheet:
82p
47p + 56p
150n
120n
180n
Shelf Filter
56p
68P
68p
-14.6dB, -7dB @ 5.5 MHz
56MHz, notches 88-108MHz
60 MHz LPF section

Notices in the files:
parts and their libraries:
LICENSE: MIT
